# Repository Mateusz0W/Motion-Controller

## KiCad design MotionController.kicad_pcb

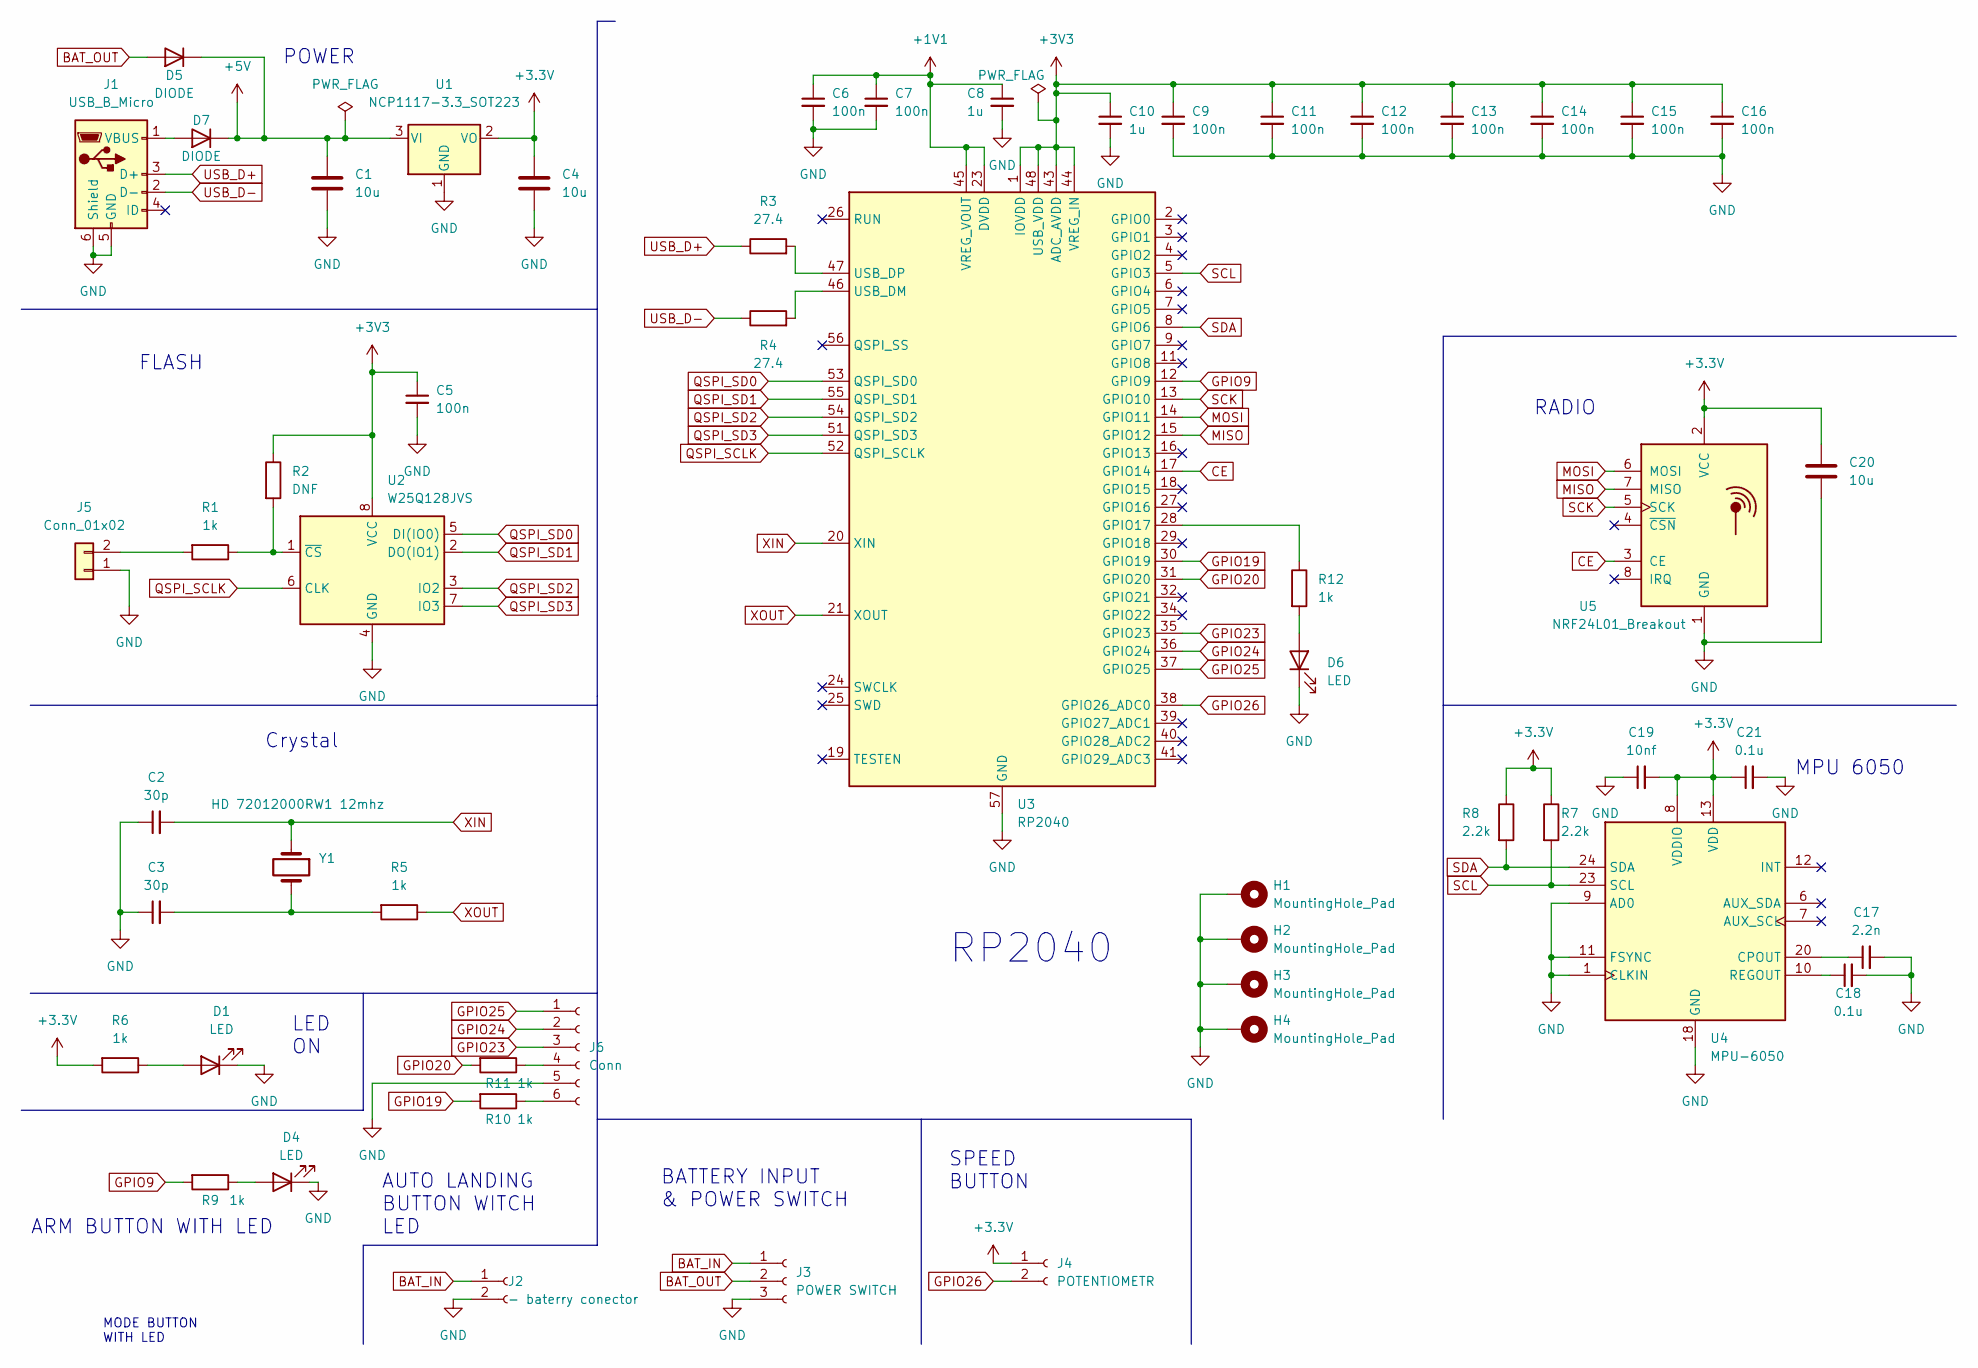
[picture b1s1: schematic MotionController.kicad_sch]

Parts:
C1, C4, C20: 10u; C_0805_2012Metric
C2, C3: 30p; C_0603_1608Metric
C5, C6, C7, C9, C11, C12, C13, C14, C15, C16: 100n; C_0402_1005Metric
C8, C10: 1u; C_0603_1608Metric
C17: 2.2n; C_0805_2012Metric
C18, C21: 0.1u; C_0402_1005Metric
C19: 10nf; C_0805_2012Metric
D1: LED; LED_0603_1608Metric
D4: LED; PinHeader_1x02_P2.54mm_Vertical
D5, D7: DIODE; D_SOD-123F
D6: LED; LED_0805_2012Metric
H1, H2, H3, H4: MountingHole_Pad; MountingHole_2.5mm_Pad_Via
J1: USB_B_Micro; USB_Micro-B_Amphenol_10118194_Horizontal
J2: - baterry conector; PinHeader_1x02_P2.54mm_Vertical
J3: POWER SWITCH; PinHeader_1x03_P2.54mm_Vertical
J4: POTENTIOMETR; PinHeader_1x02_P2.54mm_Vertical
J5: Conn_01x02; PinHeader_1x02_P2.54mm_Vertical
J6: Conn; PinHeader_1x06_P2.54mm_Vertical
R1, R5, R6, R9, R10, R11, R12: 1k; R_0805_2012Metric
R2: DNF; R_0805_2012Metric
R3, R4: 27.4; R_0402_1005Metric
R7, R8: 2.2k; R_0805_2012Metric
U1: NCP1117-3.3_SOT223; SOT-223-3_TabPin2
U2: W25Q128JVS; SOIC-8_5.23x5.23mm_P1.27mm
U3: RP2040; QFN-56-1EP_7x7mm_P0.4mm_EP3.2x3.2mm
U4: MPU-6050; InvenSense_QFN-24_4x4mm_P0.5mm
U5: NRF24L01_Breakout; nRF24L01_Breakout
Y1: HD 72012000RW1 12mhz; Crystal_SMD_HC49-SD

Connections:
+1V1: C6.1, C7.1, C8.1, U3.23 (DVDD), U3.45 (VREG_VOUT), U3.50 (DVDD)
+3.3V: C4.1, C19.2, C20.1, C21.1, J4.1, R6.2, R7.1, R8.1, U1.2 (VO), U4.8 (VDDIO), U4.13 (VDD), U5.2 (VCC)
+3V3: C5.1, C9.1, C10.1, C11.1, C12.1, C13.1, C14.1, C15.1, C16.1, R2.1, U2.8 (VCC), U3.1 (IOVDD), U3.10 (IOVDD), U3.22 (IOVDD), U3.33 (IOVDD), U3.42 (IOVDD), U3.43 (ADC_AVDD), U3.44 (VREG_IN), U3.48 (USB_VDD), U3.49 (IOVDD)
+5V: C1.1, D5.2 (K), D7.2 (K), U1.3 (VI)
BAT_IN: J2.1, J3.1
BAT_OUT: D5.1 (A), J3.2
CE: U3.17 (GPIO14), U5.3 (CE)
GND: C1.2, C2.1, C3.1, C4.2, C5.2, C6.2, C7.2, C8.2, C9.2, C10.2, C11.2, C12.2, C13.2, C14.2, C15.2, C16.2, C17.2, C18.2, C19.1, C20.2, C21.2, D1.1 (K), D4.1 (K), D6.1 (K), H1.1, H2.1, H3.1, H4.1, J1.5 (GND), J1.6 (Shield), J2.2, J3.3, J5.1, J6.5, U1.1 (GND), U2.4 (GND), U3.57 (GND), U4.1 (CLKIN), U4.9 (AD0), U4.11 (FSYNC), U4.18 (GND), U5.1 (GND)
GPIO9: R9.2, U3.12 (GPIO9)
GPIO19: R10.2, U3.30 (GPIO19)
GPIO20: R11.2, U3.31 (GPIO20)
GPIO23: J6.3, U3.35 (GPIO23)
GPIO24: J6.2, U3.36 (GPIO24)
GPIO25: J6.1, U3.37 (GPIO25)
GPIO26: J4.2, U3.38 (GPIO26_ADC0)
MISO: U3.15 (GPIO12), U5.7 (MISO)
MOSI: U3.14 (GPIO11), U5.6 (MOSI)
unnamed: C3.2, R5.2, Y1.2
unnamed: C17.1, U4.20 (CPOUT)
unnamed: C18.1, U4.10 (REGOUT)
unnamed: D1.2 (A), R6.1
unnamed: D4.2 (A), R9.1
unnamed: D6.2 (A), R12.2
unnamed: D7.1 (A), J1.1 (VBUS)
unnamed: J5.2, R1.2
unnamed: J6.4, R11.1
unnamed: J6.6, R10.1
unnamed: R1.1, R2.2, U2.1 (~CS)
unnamed: R3.2, U3.47 (USB_DP)
unnamed: R4.2, U3.46 (USB_DM)
unnamed: R12.1, U3.28 (GPIO17)
QSPI_SCLK: U2.6 (CLK), U3.52 (QSPI_SCLK)
QSPI_SD0: U2.5 (DI(IO0)), U3.53 (QSPI_SD0)
QSPI_SD1: U2.2 (DO(IO1)), U3.55 (QSPI_SD1)
QSPI_SD2: U2.3 (IO2), U3.54 (QSPI_SD2)
QSPI_SD3: U2.7 (IO3), U3.51 (QSPI_SD3)
SCK: U3.13 (GPIO10), U5.5 (SCK)
SCL: R7.2, U3.5 (GPIO3), U4.23 (SCL)
SDA: R8.2, U3.8 (GPIO6), U4.24 (SDA)
USB_D+: J1.3 (D+), R3.1
USB_D-: J1.2 (D-), R4.1
XIN: C2.2, U3.20 (XIN), Y1.1
XOUT: R5.1, U3.21 (XOUT)

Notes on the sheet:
MPU 6050
ARM BUTTON WITH LED
SPEED BUTTON
MODE BUTTON WITH LED
BATTERY INPUT & POWER SWITCH
AUTO LANDING BUTTON WITCH LED
POWER
LED ON
RP2040
FLASH
Crystal
RADIO

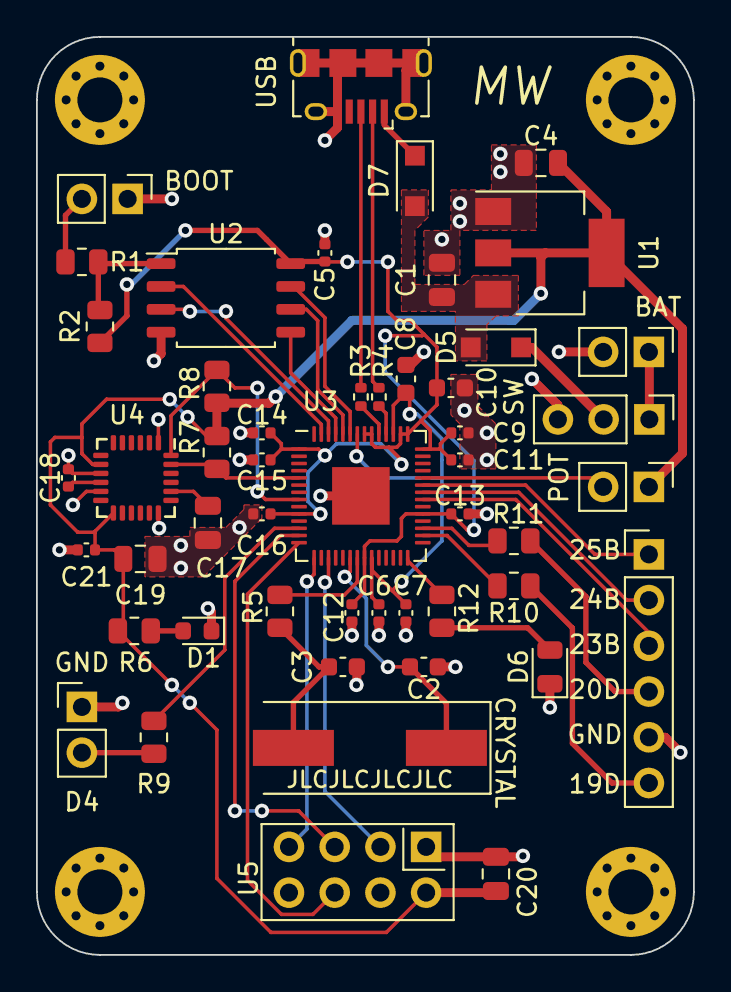
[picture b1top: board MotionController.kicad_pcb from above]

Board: 2 copper layers, 36.5 x 51.0 mm, 54 parts (0 on the bottom side), 43 nets.

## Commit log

2024-04-12 upload
